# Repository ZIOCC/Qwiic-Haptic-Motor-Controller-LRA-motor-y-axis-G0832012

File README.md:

# Qwiic Haptic Motor Controller LRA Motor Round G0832012 (Y-Axis)

> This product can be available for purchase [here](https://www.smart-prototyping.com/Zio-Qwiic-Haptic-Motor-Controller-Motor-y-axis-G0832012).

#### Description

We are making your life easier, this is the first Motor controller IC (DRV2605L) + LRA motor (G0832012) combination module on the marketing, we make it tiny and with two Qwiic connectors on the board, no need soldering, just plugin and have fun!

To make the board smaller, you can use pliers to remove the tab bar by following the continuously hole line. 

About the LRA motor (Y-Axis, G0832012)
This is a general construction LRA vibration motor, the Y-axis type. Those readers familiar with audio engineering will note that the voice coil drive is very similar to that loudspeaker. However, instead of a cone that generates sound pressure waves, there is a mass that generates vibrations.

> Check the source documentation [here](https://www.precisionmicrodrives.com/vibration-motors/linear-resonant-actuators-lras/).

#### Specification

* Motor Driver IC: DRV2605L
* Y-Axis Motor Manufacture Number:
* IC:D RV2605L
* I2C address: 0x5A
* Dimension: 35.9 x 14.4mm
* Weight: 2.9g

#### Links

* [PCB Source file](https://github.com/ZIOCC/Qwiic-Haptic-Motor-Controller-LRA-motor-y-axis-G0832012/tree/master/EAGLE)
* [PCB Schematic](https://github.com/ZIOCC/Qwiic-Haptic-Motor-Controller-LRA-motor-y-axis-G0832012/blob/master/Haptic%20Motor%20driver%20board%20%2B%20LRA%20y%20axis%20G0832012.pdf)
* [Demo Code (Adafruit DRV2605 Library)](https://github.com/adafruit/Adafruit_DRV2605_Library)
* [DRV2605L Datasheet](https://www.smart-prototyping.com/image/data/2_components/sensors/101802DRV2605L%20Haptic%20Driver/DRV2605.pdf)

###### About Zio
> Zio is a new line of open sourced, compact, and grid layout boards, fully integrated for Arduino and Qwiic ecosystem. Designed ideally for wearables, robotics, small-space limitations or other on the go projects. Check out other awesome Zio products [here](https://www.smart-prototyping.com/Zio).

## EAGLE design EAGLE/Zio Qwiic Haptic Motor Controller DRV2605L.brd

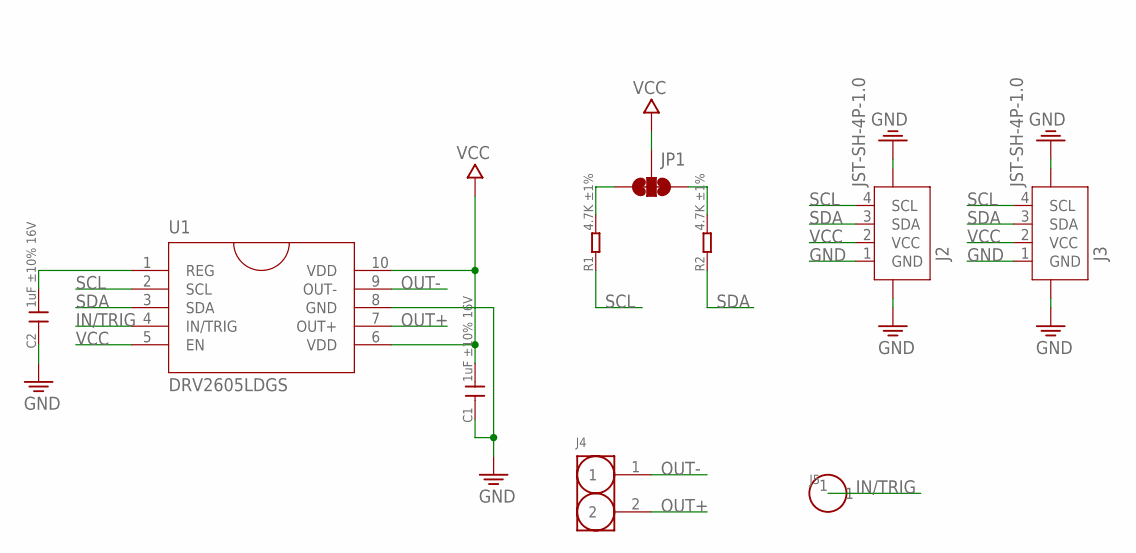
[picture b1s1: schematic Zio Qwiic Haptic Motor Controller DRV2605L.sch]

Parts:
C1, C2: 1uF ±10% 16V; C0603
J2, J3: JST-SH-4P-1.0; JST-SH-4P
J4: HEADER-2P-2.0; 2P-2.0
J5: HEADER-1P; 1P-40MIL
JP1: SMT-JUMPER_3_2-NC_TRACE
R1, R2: 4.7K ±1%; R0402
U1: DRV2605LDGS; VSSOP10

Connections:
GND: C1.1, C2.1, J2.1 (GND), J2.NC1 (5), J2.NC2 (6), J3.1 (GND), J3.NC1 (5), J3.NC2 (6), U1.8 (GND)
IN/TRIG: J5.1, U1.4 (IN/TRIG)
unnamed: C2.2, U1.1 (REG)
unnamed: JP1.3, R1.2
unnamed: JP1.1, R2.2
OUT+: J4.2, U1.7 (OUT+)
OUT-: J4.1, U1.9 (OUT-)
SCL: J2.4 (SCL), J3.4 (SCL), R1.1, U1.2 (SCL)
SDA: J2.3 (SDA), J3.3 (SDA), R2.1, U1.3 (SDA)
VCC: C1.2, J2.2 (VCC), J3.2 (VCC), JP1.2, U1.5 (EN), U1.6 (VDD), U1.10 (VDD)

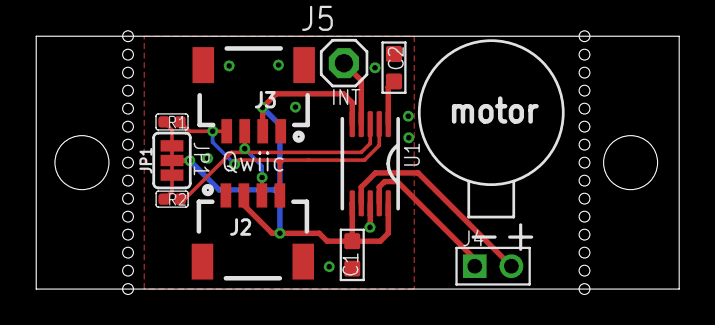
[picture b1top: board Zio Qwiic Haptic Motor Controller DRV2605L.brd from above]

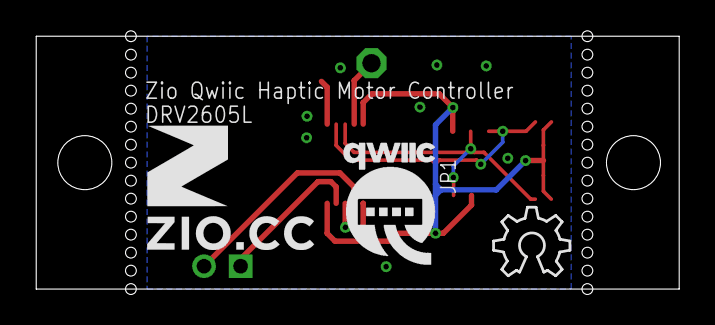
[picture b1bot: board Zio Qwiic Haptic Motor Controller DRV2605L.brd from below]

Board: 2 copper layers, 35.7 x 14.0 mm, 13 parts (3 on the bottom side), 10 nets.

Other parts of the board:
U$1: 7MM
U$2: OSHW_6X150_NOTEXT
U$5: QWIIC-LOGO-MEDIUM
